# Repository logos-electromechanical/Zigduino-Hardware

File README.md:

Zigduino-Hardware
=================

Hardware repository for the Zigduino

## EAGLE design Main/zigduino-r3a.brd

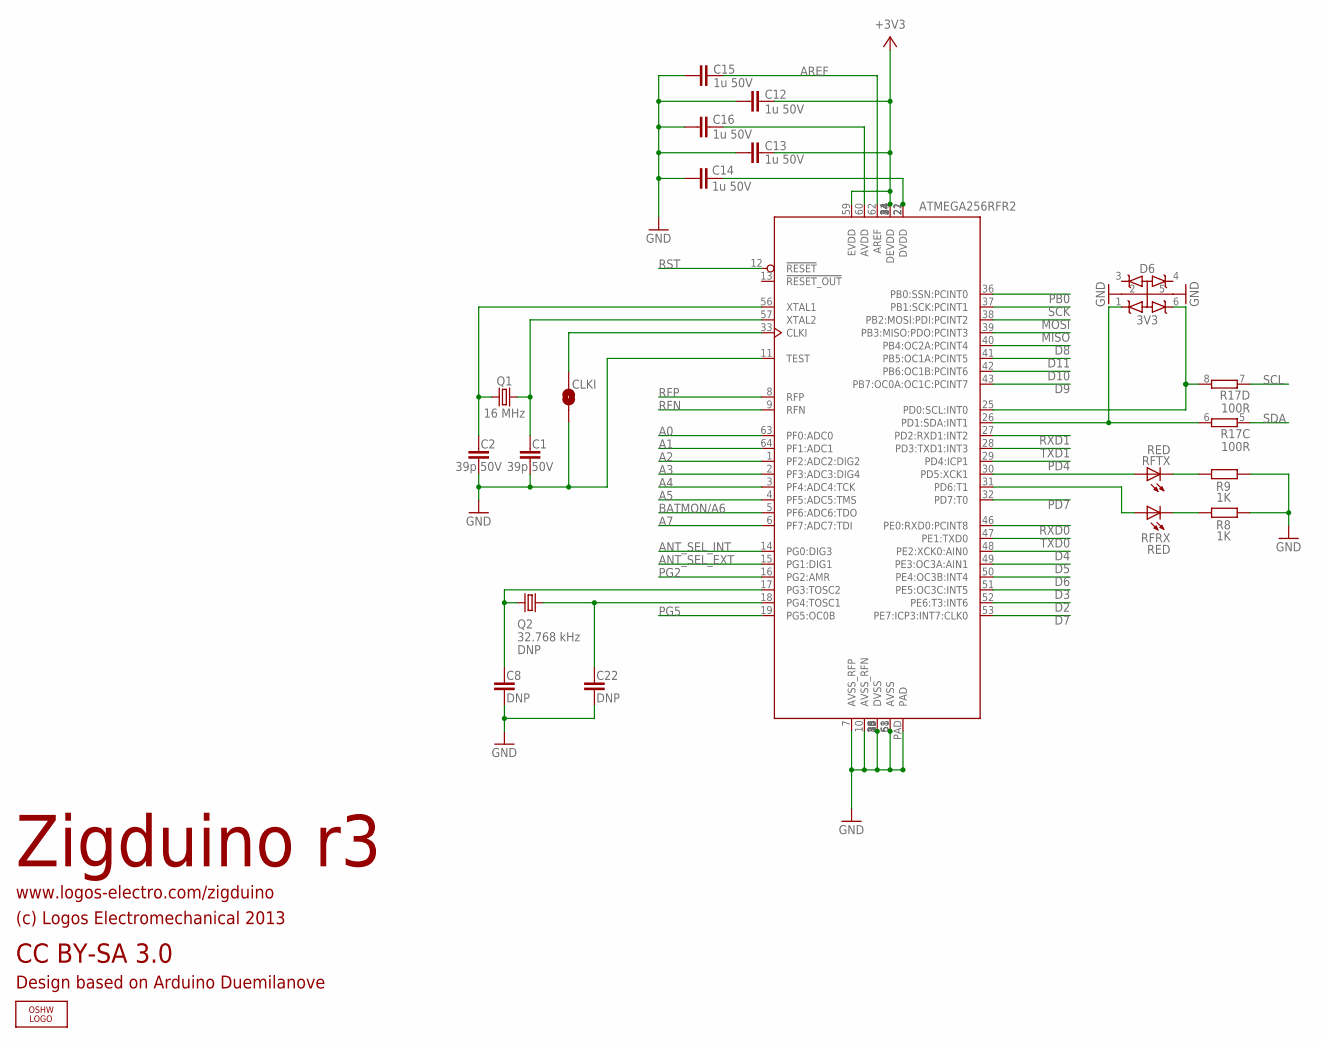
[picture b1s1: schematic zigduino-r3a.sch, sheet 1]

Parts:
C1, C2: 39p 50V; C0603; PARTNO C1608C0G1H390J
C8, C22: DNP; C0603
C12, C13, C14, C15, C16: 1u 50V; C0603
CLKI: SOLDERJUMPERTRACE; SJ_2S-TRACE
D6: 3V3; SC74_INFINEON
LOGO1: OSHW_LOGO_FILLX0200-NT; OSHW_FILLX200_NOTEXT
Q1: 16 MHz; CSM-3X; PARTNO ECS-160-20-3X-TR
Q2: 32.768 kHz; TC26H
R8, R9: 1K; R0603; PARTNO RMCF0603FT1K00
R17: 100R; CTS742C083-RES; PARTNO 742C083101JPTR
RFRX: RED; CHIP-LED0603; PARTNO LTST-C193KRKT-5A
RFTX: RED; CHIP-LED0603; PARTNO LTST-C193KRKT-5A
U3: ATMEGA128RFA1; QFN64; PARTNO ATMEGA128RFA1-ZUR

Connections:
+3V3: C12.1, C13.1, U3.23 (DEVDD), U3.34 (DEVDD), U3.44 (DEVDD), U3.54 (DEVDD), U3.59 (EVDD); also elsewhere on the board
A0: U3.63 (PF0:ADC0); also elsewhere on the board
A1: U3.64 (PF1:ADC1); also elsewhere on the board
A2: U3.1 (PF2:ADC2:DIG2); also elsewhere on the board
A3: U3.2 (PF3:ADC3:DIG4); also elsewhere on the board
A4: U3.3 (PF4:ADC4:TCK); also elsewhere on the board
A5: U3.4 (PF5:ADC5:TMS); also elsewhere on the board
A7: U3.6 (PF7:ADC7:TDI); also elsewhere on the board
ANT_SEL_EXT: U3.15 (PG1:DIG1); also elsewhere on the board
ANT_SEL_INT: U3.14 (PG0:DIG3); also elsewhere on the board
AREF: C15.2, U3.62 (AREF); also elsewhere on the board
BATMON/A6: U3.5 (PF6:ADC6:TDO); also elsewhere on the board
D2: U3.52 (PE6:T3:INT6); also elsewhere on the board
D3: U3.51 (PE5:OC3C:INT5); also elsewhere on the board
D4: U3.48 (PE2:XCK0:AIN0); also elsewhere on the board
D5: U3.49 (PE3:OC3A:AIN1); also elsewhere on the board
D6: U3.50 (PE4:OC3B:INT4); also elsewhere on the board
D7: U3.53 (PE7:ICP3:INT7:CLK0); also elsewhere on the board
D8: U3.40 (PB4:OC2A:PCINT4); also elsewhere on the board
D9: U3.43 (PB7:OC0A:OC1C:PCINT7); also elsewhere on the board
D10: U3.42 (PB6:OC1B:PCINT6); also elsewhere on the board
D11: U3.41 (PB5:OC1A:PCINT5); also elsewhere on the board
GND: C1.1, C2.1, C8.1, C12.2, C13.2, C14.2, C15.1, C16.1, C22.1, CLKI.2, D6.2 (G2), D6.5 (G5), R8.1, R9.1, U3.7 (AVSS_RFP), U3.10 (AVSS_RFN), U3.11 (TEST), U3.20 (DVSS), U3.24 (DVSS), U3.35 (DVSS), U3.45 (DVSS), U3.55 (DVSS), U3.58 (AVSS), U3.61 (AVSS), U3.PAD; also elsewhere on the board
MISO: U3.39 (PB3:MISO:PDO:PCINT3); also elsewhere on the board
MOSI: U3.38 (PB2:MOSI:PDI:PCINT2); also elsewhere on the board
unnamed: R9.2, RFTX.C
unnamed: C1.2, Q1.1, U3.57 (XTAL2)
unnamed: C2.2, Q1.2, U3.56 (XTAL1)
unnamed: D6.6 (Z6), R17.8 (2), U3.25 (PD0:SCL:INT0)
unnamed: D6.1 (Z1), R17.6 (2), U3.26 (PD1:SDA:INT1)
unnamed: R8.2, RFRX.C
unnamed: CLKI.1, U3.33 (CLKI)
unnamed: C14.1, U3.21 (DVDD), U3.22 (DVDD)
unnamed: C16.2, U3.60 (AVDD)
unnamed: C8.2, Q2.2, U3.17 (PG3:TOSC2)
unnamed: C22.2, Q2.1, U3.18 (PG4:TOSC1)
PB0: U3.36 (PB0:SSN:PCINT0); also elsewhere on the board
PD4: U3.29 (PD4:ICP1); also elsewhere on the board
PD7: U3.32 (PD7:T0); also elsewhere on the board
PG2: U3.16 (PG2:AMR); also elsewhere on the board
PG5: U3.19 (PG5:OC0B); also elsewhere on the board
RFN: U3.9 (RFN); also elsewhere on the board
RFP: U3.8 (RFP); also elsewhere on the board
RFRX: RFRX.A, U3.31 (PD6:T1)
RFTX: RFTX.A, U3.30 (PD5:XCK1)
RST: U3.12 (!RESET!); also elsewhere on the board
RXD0: U3.46 (PE0:RXD0:PCINT8); also elsewhere on the board
RXD1: U3.27 (PD2:RXD1:INT2); also elsewhere on the board
SCK: U3.37 (PB1:SCK:PCINT1); also elsewhere on the board
SCL: R17.7 (1); also elsewhere on the board
SDA: R17.5 (1); also elsewhere on the board
TXD0: U3.47 (PE1:TXD0); also elsewhere on the board
TXD1: U3.28 (PD3:TXD1:INT3); also elsewhere on the board

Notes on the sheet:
Zigduino r3
CC BY-SA 3.0
(c) Logos Electromechanical 2013
www.logos-electro.com/zigduino
ATMEGA256RFR2
Design based on Arduino Duemilanove
DNP

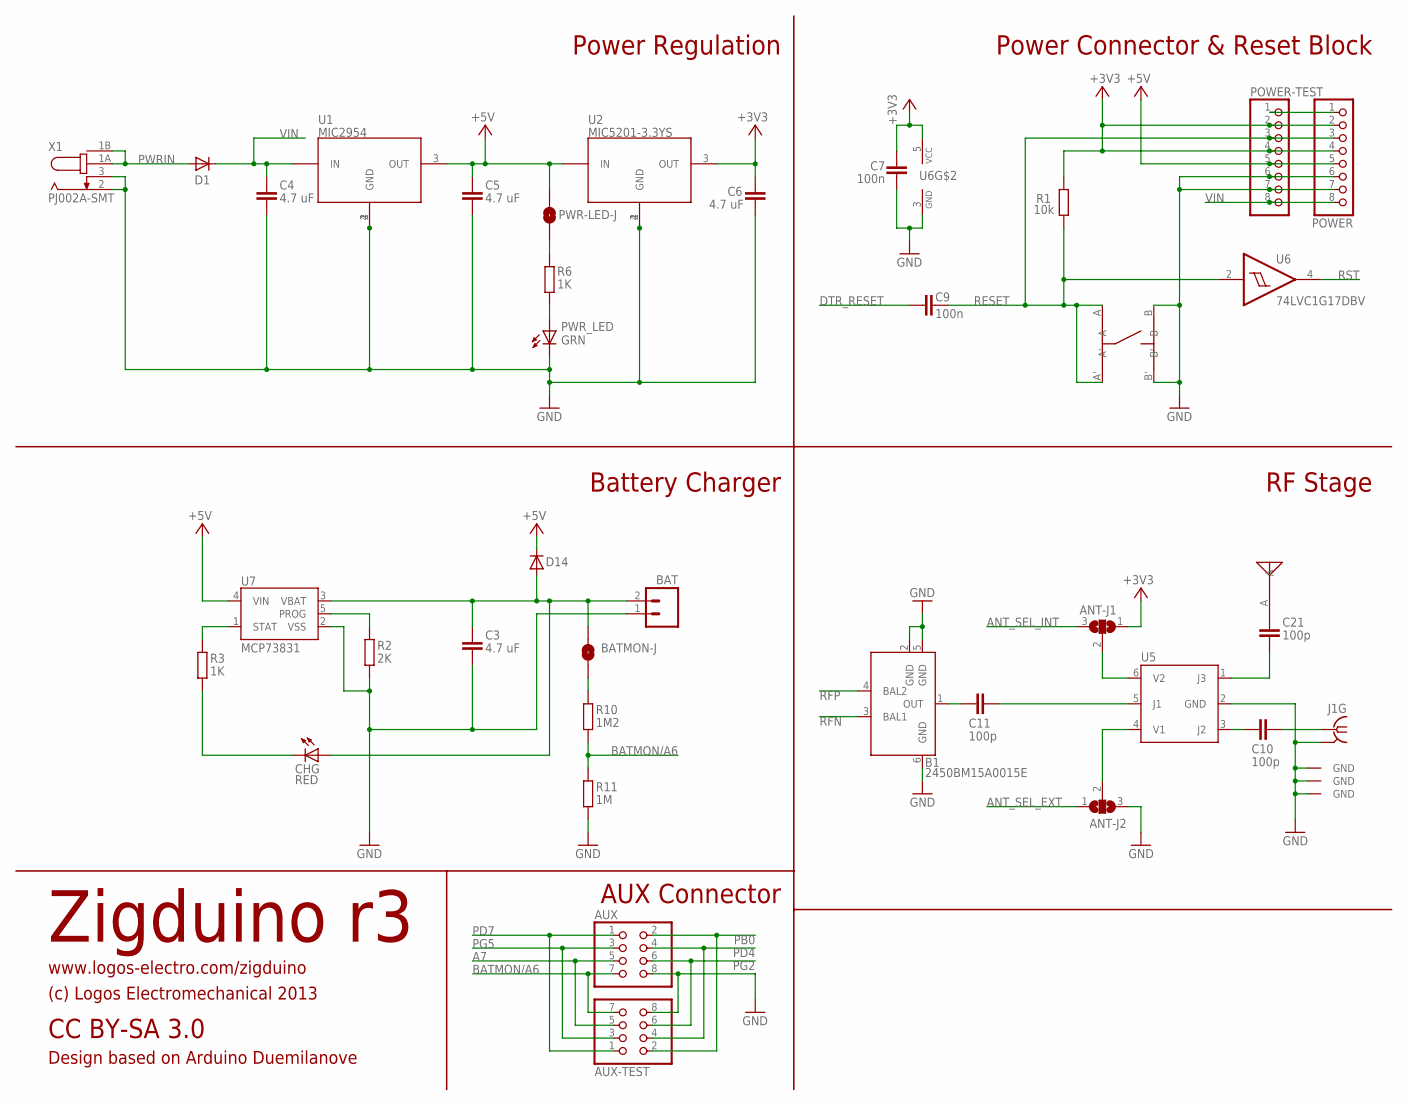
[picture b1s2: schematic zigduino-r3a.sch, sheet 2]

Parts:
ANT1: MOLEX-ANT; PARTNO 0479480001
ANT-J1: SOLDERJUMPER_2WAYSHORT1&2; SJ_3_SHORT1&2
ANT-J2: SOLDERJUMPER_2WAYSHORT2&3; SJ_3_SHORT2&3
AUX: PINHD-2X4_2.54-SMD; 2X04SMD
AUX-TEST: PINHD-2X4TEST; 2X04-TEST
B1: 2450BM15A0015E; WURTH-BALUN
BAT: M02-JST-2MM-SMT; S2B-PH; PARTNO S2B-PH-SM4-TB(LF)(SN)
BATMON-J: SOLDERJUMPERTRACE; SJ_2S-TRACE
C3, C4, C5, C6: 4.7 uF; C1206; PARTNO C3216Y5V1H475Z
C7, C9: 100n; C0603; PARTNO CC0603MRY5V9BB104
C10, C11, C21: 100p; C0603
CHG: RED; CHIP-LED0603; PARTNO LTST-C193KRKT-5A
D1, D14: DIODESOD-123; SOD-123; PARTNO B150B-13-F
J1: CONNREVSMA003.062; EDGE-RSMA
POWER: PINHD-1X8_2.54-SMD; 1X08SMD; PARTNO 19743
POWER-TEST: PINHD-1X8TEST; 1X08-TEST
PWR-LED-J: SOLDERJUMPERTRACE; SJ_2S-TRACE
PWR_LED: GRN; CHIP-LED0603; PARTNO LTST-C193KGKT-5A
R1: 10k; R0603; PARTNO RMCF0603FT10K0
R2: 2K; R0603; PARTNO RC0603FR-072KL
R3, R6: 1K; R0603; PARTNO RMCF0603FT1K00
R10: 1M2; R0603; PARTNO ERJ-3EKF1204V
R11: 1M; R0603; PARTNO ERJ-3EKF1004V
SW1: EVQ-PSD02K; EVQPSD02K; PARTNO EVQ-PSD02K
U1: MIC2954; SOT223; PARTNO MIC2954-03WS-TR
U2: MIC5201-3.3YS; SOT223; PARTNO MIC5201-3.3YS TR
U5: AS222-92LF; SC70-6L
U6: 74LVC1G17DBV; SOT23-5; PARTNO SN74LVC1G17DBVR
U7: MCP73831; SOT23-5; PARTNO MCP73831T-2ACI/OT
X1: PJ002A-SMT; PARTNO PJ-002AH-SMT

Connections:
+3V3: ANT-J1.1, C6.1, C7.2, POWER.2, POWER.4, POWER-TEST.2, POWER-TEST.4, R1.2, U2.3 (OUT), U6.5 (VCC); also elsewhere on the board
+5V: C5.1, D14.C, POWER.5, POWER-TEST.5, PWR-LED-J.2, U1.3 (OUT), U2.1 (IN), U7.4 (VIN); also elsewhere on the board
A7: AUX.5, AUX-TEST.5; also elsewhere on the board
ANT_SEL_EXT: ANT-J2.1; also elsewhere on the board
ANT_SEL_INT: ANT-J1.3; also elsewhere on the board
BATMON/A6: AUX.7, AUX-TEST.7, R10.2, R11.1; also elsewhere on the board
DTR_RESET: C9.1; also elsewhere on the board
GND: ANT-J2.3, AUX.8, AUX-TEST.8, B1.2 (GND), B1.5 (GND), B1.6 (GND), BAT.1, C3.2, C4.2, C5.2, C6.2, C7.1, J1.SHIELD@0 (GND), J1.SHIELD@1 (GND), J1.SHIELD@2 (GND), J1.SHIELD@3 (GND), POWER.6, POWER.7, POWER-TEST.6, POWER-TEST.7, PWR_LED.C, R2.1, R11.2, SW1.B, SW1.B', U1.2 (GND), U1.4 (GND), U2.2 (GND), U2.4 (GND), U5.2 (GND), U6.3 (GND), U7.2 (VSS), X1.2, X1.3; also elsewhere on the board
unnamed: PWR_LED.A, R6.2
unnamed: PWR-LED-J.1, R6.1
unnamed: BATMON-J.1, R10.1
unnamed: B1.1 (OUT), C11.2
unnamed: C11.1, U5.5 (J1)
unnamed: C10.2, U5.3 (J2)
unnamed: R2.2, U7.5 (PROG)
unnamed: R3.1, U7.1 (STAT)
unnamed: CHG.C, R3.2
unnamed: C21.2, U5.1 (J3)
unnamed: C10.1, J1.CENTER (1)
unnamed: POWER.1, POWER-TEST.1
unnamed: ANT1.A, C21.1
unnamed: ANT-J2.2, U5.4 (V1)
unnamed: ANT-J1.2, U5.6 (V2)
PB0: AUX.2, AUX-TEST.2; also elsewhere on the board
PD4: AUX.4, AUX-TEST.4; also elsewhere on the board
PD7: AUX.1, AUX-TEST.1; also elsewhere on the board
PG2: AUX.6, AUX-TEST.6; also elsewhere on the board
PG5: AUX.3, AUX-TEST.3; also elsewhere on the board
PWRIN: D1.A, X1.1A, X1.1B
RESET: C9.2, POWER.3, POWER-TEST.3, R1.1, SW1.A, SW1.A', U6.2 (I); also elsewhere on the board
RFN: B1.3 (BAL1); also elsewhere on the board
RFP: B1.4 (BAL2); also elsewhere on the board
RST: U6.4 (O); also elsewhere on the board
VBAT: BAT.2, BATMON-J.2, C3.1, CHG.A, D14.A, U7.3 (VBAT); also elsewhere on the board
VIN: C4.1, D1.C, POWER.8, POWER-TEST.8, U1.1 (IN)

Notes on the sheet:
Zigduino r3
CC BY-SA 3.0
(c) Logos Electromechanical 2013
www.logos-electro.com/zigduino
Design based on Arduino Duemilanove
AUX Connector
Battery Charger
Power Regulation
RF Stage
Power Connector & Reset Block

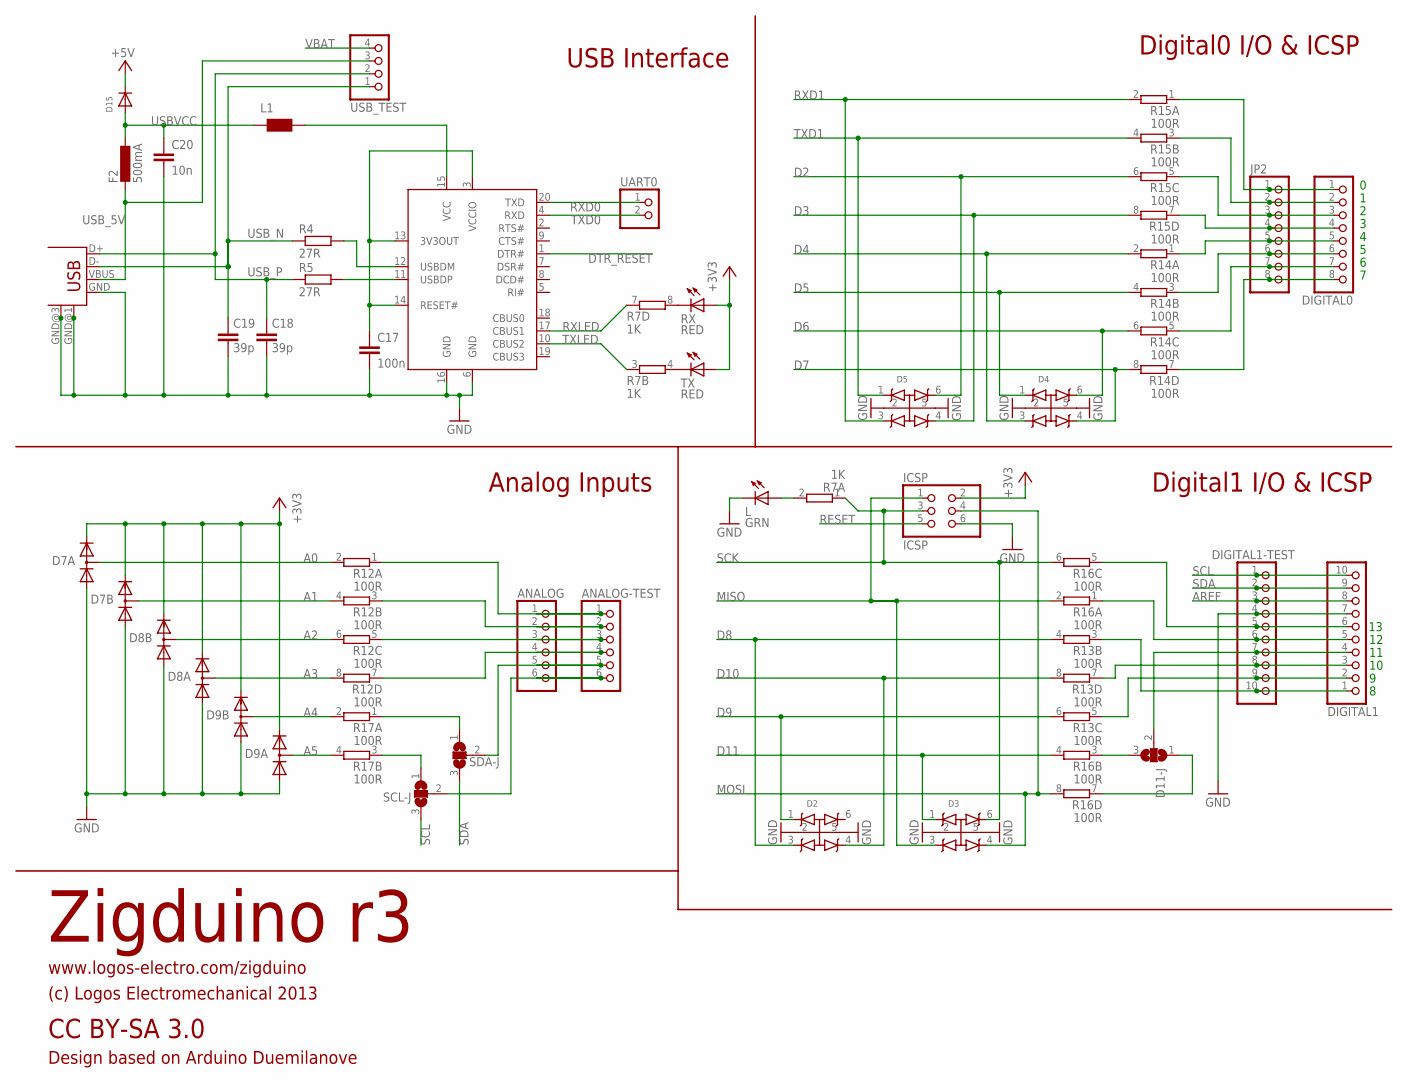
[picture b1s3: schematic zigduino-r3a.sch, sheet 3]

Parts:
ANALOG: PINHD-1X6_2.54-SMD; 1X06SMD; PARTNO 19742
ANALOG-TEST: PINHD-1X6TEST; 1X06-TEST
C17: 100n; C0603; PARTNO CC0603MRY5V9BB104
C18, C19: 39p; C0603; PARTNO C1608C0G1H390J
C20: 10n; C0603; PARTNO GRM188R71H103KA01D
D2, D3, D4, D5: PESD3V3S4UD; SC74_INFINEON
D7, D8, D9: SD103ASDM; SOT26; PARTNO SD103ASDM-7
D11-J: SOLDERJUMPER_2WAYSHORT2&3; SJ_3_SHORT2&3
D15: DIODESOD-123; SOD-123; PARTNO B150B-13-F
DIGITAL0: PINHD-1X8_2.54-SMD; 1X08SMD; PARTNO 19743
DIGITAL1: PINHD-1X10_2.54-SMD; 1X10SMD; PARTNO 20083
DIGITAL1-TEST: PINHD-1X10TEST; 1X10-TEST
F2: 500mA; L1812; PARTNO MF-MSMF050-2
ICSP: ICSP; 2X03; PARTNO 961206-6404-AR
JP2: PINHD-1X8TEST; 1X08-TEST
L: GRN; CHIP-LED0603; PARTNO LTST-C193KGKT-5A
L1: WE-CBF_0805; 0805; PARTNO MI0805K400R-10
R4, R5: 27R; R0603; PARTNO RC0603JR-0727RL
R7: 1K; CTS742C083-RES; PARTNO 742C083102JPTR
R12, R13, R14, R15, R16, R17: 100R; CTS742C083-RES; PARTNO 742C083101JPTR
RX: RED; CHIP-LED0603; PARTNO LTST-C193KRKT-5A
SCL-J: SOLDERJUMPER_2WAYSHORT2&3; SJ_3_SHORT2&3
SDA-J: SOLDERJUMPER_2WAYSHORT2&3; SJ_3_SHORT2&3
TX: RED; CHIP-LED0603; PARTNO LTST-C193KRKT-5A
U4: FT231XS-R; SSOP20; PARTNO FT231XS-R
UART0: PINHD-1X2; 1X02; PARTNO 00522
USB: USB-MB-S; PARTNO 20236
USB_TEST: PINHD-1X4TEST; 1X04-TEST

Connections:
+3V3: D7.2 (C), D7.5 (C), D8.2 (C), D8.5 (C), D9.2 (C), D9.5 (C), ICSP.2, RX.A, TX.A; also elsewhere on the board
+5V: D15.C; also elsewhere on the board
A0: D7.4 (AC), R12.2; also elsewhere on the board
A1: D7.1 (AC), R12.4 (2); also elsewhere on the board
A2: D8.1 (AC), R12.6 (2); also elsewhere on the board
A3: D8.4 (AC), R12.8 (2); also elsewhere on the board
A4: D9.1 (AC), R17.2; also elsewhere on the board
A5: D9.4 (AC), R17.4 (2); also elsewhere on the board
AREF: DIGITAL1.8, DIGITAL1-TEST.3; also elsewhere on the board
D2: D5.6 (Z6), R15.6 (2); also elsewhere on the board
D3: D5.4 (Z4), R15.8 (2); also elsewhere on the board
D4: D4.3 (Z3), R14.2; also elsewhere on the board
D5: D4.1 (Z1), R14.4 (2); also elsewhere on the board
D6: D4.6 (Z6), R14.6 (2); also elsewhere on the board
D7: D4.4 (Z4), R14.8 (2); also elsewhere on the board
D8: D2.3 (Z3), R13.4 (2); also elsewhere on the board
D9: D2.1 (Z1), R13.6 (2); also elsewhere on the board
D10: D2.4 (Z4), R13.8 (2); also elsewhere on the board
D11: D3.1 (Z1), R16.4 (2); also elsewhere on the board
DTR_RESET: U4.1 (DTR#); also elsewhere on the board
GND: C17.2, C18.2, C19.2, C20.2, D2.2 (G2), D2.5 (G5), D3.2 (G2), D3.5 (G5), D4.2 (G2), D4.5 (G5), D5.2 (G2), D5.5 (G5), D7.3 (A), D7.6 (A), D8.3 (A), D8.6 (A), D9.3 (A), D9.6 (A), DIGITAL1.7, DIGITAL1-TEST.4, ICSP.6, L.C, U4.6 (GND), U4.16 (GND), USB.GND, USB.GND@1 (GND), USB.GND@3 (GND); also elsewhere on the board
MISO: D3.3 (Z3), ICSP.1, R16.2; also elsewhere on the board
MOSI: D3.4 (Z4), ICSP.4, R16.8 (2); also elsewhere on the board
MOSI-PIN: D11-J.1, R16.7 (1)
unnamed: L.A, R7.2
unnamed: ANALOG.5, ANALOG-TEST.5, SDA-J.2
unnamed: DIGITAL0.3, JP2.3, R15.5 (1)
unnamed: DIGITAL1.5, DIGITAL1-TEST.6, R16.1
unnamed: DIGITAL0.5, JP2.5, R14.1
unnamed: DIGITAL0.7, JP2.7, R14.5 (1)
unnamed: DIGITAL0.6, JP2.6, R14.3 (1)
unnamed: DIGITAL0.4, JP2.4, R15.7 (1)
unnamed: DIGITAL0.8, JP2.8, R14.7 (1)
unnamed: DIGITAL1.6, DIGITAL1-TEST.5, R16.5 (1)
unnamed: R7.4 (2), TX.C
unnamed: C17.1, U4.3 (VCCIO), U4.13 (3V3OUT), U4.14 (RESET#)
unnamed: R7.8 (2), RX.C
unnamed: R4.2, U4.12 (USBDM)
unnamed: R5.2, U4.11 (USBDP)
unnamed: L1.2, U4.15 (VCC)
unnamed: ANALOG.6, ANALOG-TEST.6, SCL-J.2
unnamed: R17.1, SDA-J.1
unnamed: ANALOG.1, ANALOG-TEST.1, R12.1
unnamed: ANALOG.2, ANALOG-TEST.2, R12.3 (1)
unnamed: ANALOG.3, ANALOG-TEST.3, R12.5 (1)
unnamed: ANALOG.4, ANALOG-TEST.4, R12.7 (1)
unnamed: R17.3 (1), SCL-J.1
unnamed: DIGITAL1.1, DIGITAL1-TEST.10, R13.3 (1)
unnamed: D11-J.2, DIGITAL1.4, DIGITAL1-TEST.7
unnamed: DIGITAL1.2, DIGITAL1-TEST.9, R13.5 (1)
unnamed: DIGITAL0.1, JP2.1, R15.1
unnamed: DIGITAL0.2, JP2.2, R15.3 (1)
PWM-10: DIGITAL1.3, DIGITAL1-TEST.8, R13.7 (1)
PWM-11: D11-J.3, R16.3 (1)
RESET: ICSP.5; also elsewhere on the board
RXD0: U4.20 (TXD), UART0.1; also elsewhere on the board
RXD1: D5.3 (Z3), R15.2; also elsewhere on the board
RXLED: R7.7 (1), U4.17 (CBUS1)
SCK: D3.6 (Z6), ICSP.3, R7.1, R16.6 (2); also elsewhere on the board
SCL: DIGITAL1.10, DIGITAL1-TEST.1, SCL-J.3; also elsewhere on the board
SDA: DIGITAL1.9, DIGITAL1-TEST.2, SDA-J.3; also elsewhere on the board
TXD0: U4.4 (RXD), UART0.2; also elsewhere on the board
TXD1: D5.1 (Z1), R15.4 (2); also elsewhere on the board
TXLED: R7.3 (1), U4.10 (CBUS2)
USBVCC: C20.1, D15.A, F2.1, L1.1
USB_5V: F2.2, USB.VBUS, USB_TEST.3
USB_N: C19.1, R4.1, USB.D-, USB_TEST.1
USB_P: C18.1, R5.1, USB.D+, USB_TEST.2
VBAT: USB_TEST.4; also elsewhere on the board

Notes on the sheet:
Zigduino r3
CC BY-SA 3.0
(c) Logos Electromechanical 2013
www.logos-electro.com/zigduino
Design based on Arduino Duemilanove
Analog Inputs
USB Interface
Digital1 I/O & ICSP
Digital0 I/O & ICSP

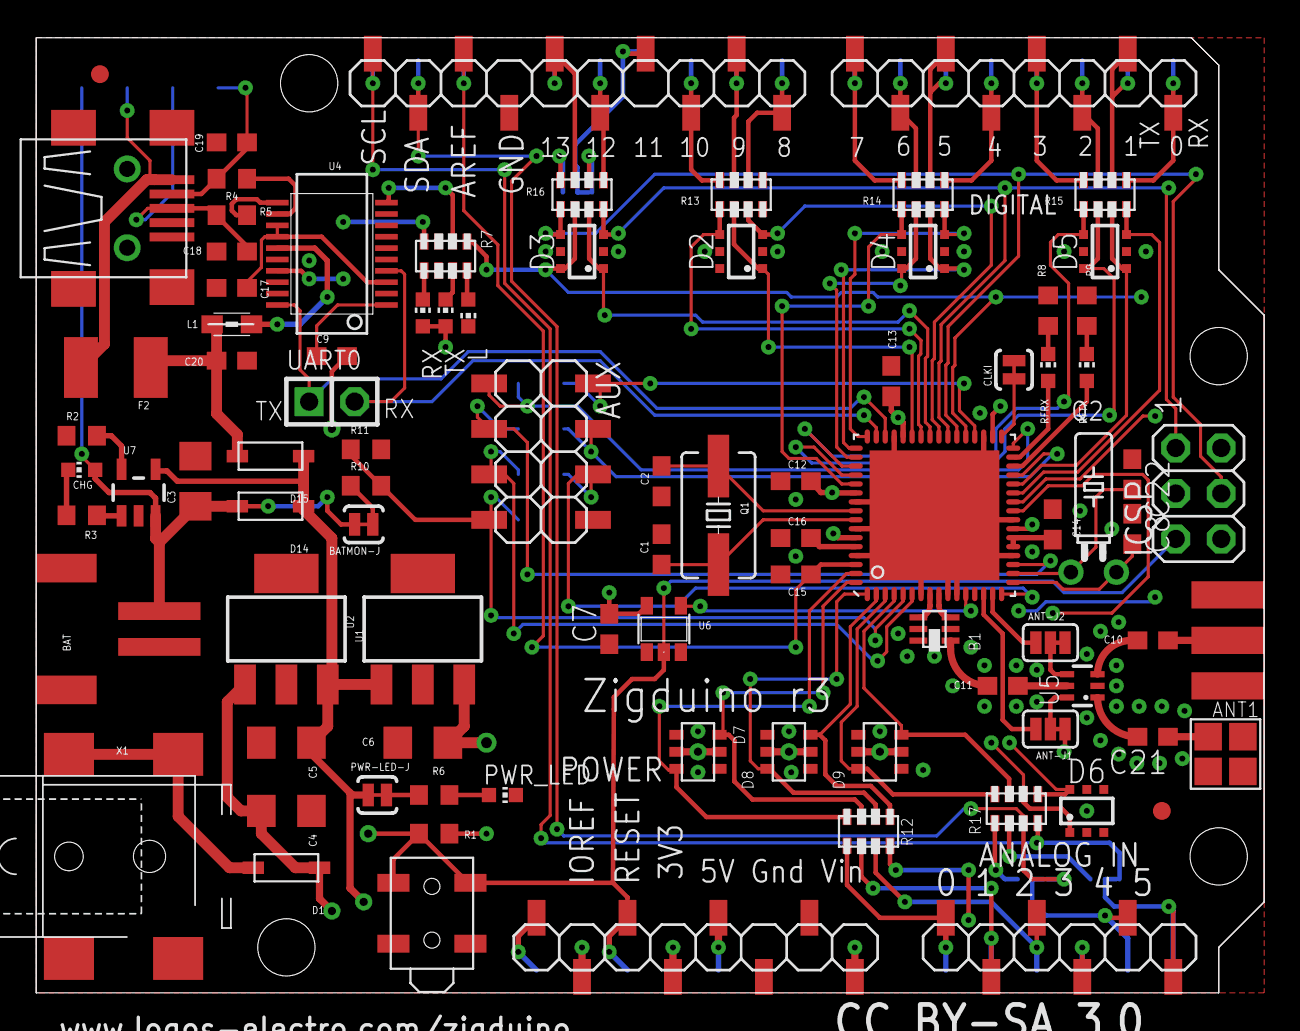
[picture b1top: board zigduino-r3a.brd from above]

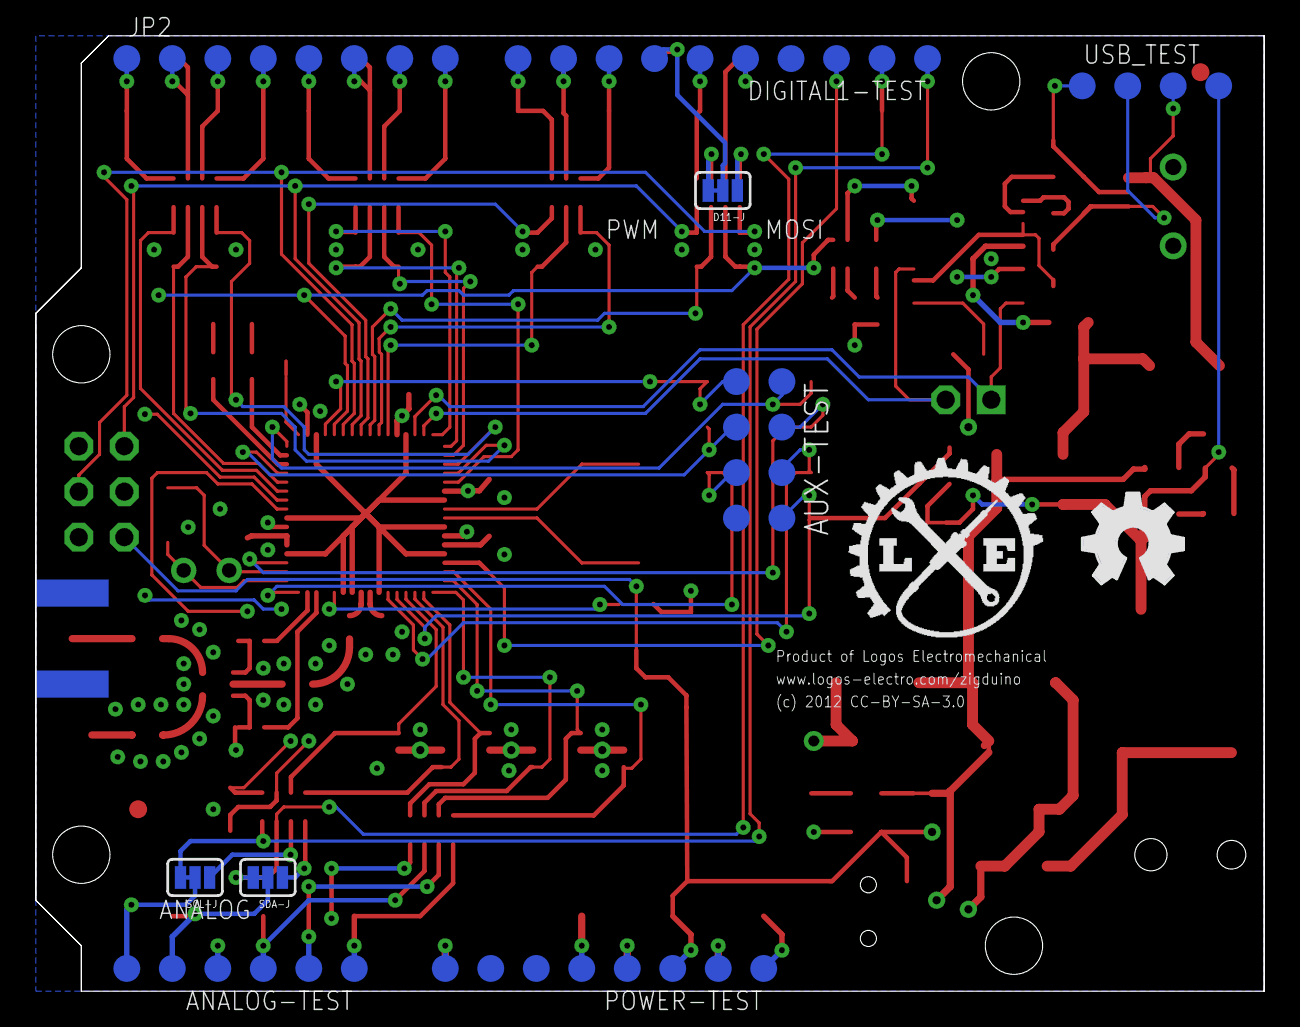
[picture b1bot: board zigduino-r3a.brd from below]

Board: 4 copper layers, 68.6 x 53.3 mm, 100 parts (11 on the bottom side), 111 nets.

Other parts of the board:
U$3, U$5: FIDUCIAL_G10
U$4: LOGO-SM

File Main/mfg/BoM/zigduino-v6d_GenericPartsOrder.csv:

Manufacturer Part Number,Description,Qty-1,Part References,Value
B150B-13-F,DIODE SCHOTTKY 50V 1A SMB,3,"D1, D14, D15",
MI0805K400R-10,FERRITE 1.5A 40 OHM 0805 SMD,1,L1,
S2B-PH-SM4-TB(LF)(SN),CONN HEADER PH SIDE 2POS 2MM SMD,1,JP1,
742C083102JPTR,RES ARRAY 1K OHM 8TERM 4RES SMD,1,R7,1K
RMCF0603FT1K00,RES 1K OHM 1/10W 1% 0603 SMD,4,"R3, R6, R8, R9",1K
ERJ-3EKF1004V,RES 1.00M OHM 1/10W 1% 0603 SMD,1,R11,1M
ERJ-3EKF1204V,RES 1.20M OHM 1/10W 1% 0603 SMD,1,R10,1M2
RC0603FR-072KL,RES 2.00K OHM 1/10W 1% 0603 SMD,1,R2,2K
C3216Y5V1H475Z,CAP CER 4.7UF 50V Y5V 1206,4,"C3, C4, C5, C6",4.7 uF
RMCF0603FT10K0,RES 10K OHM 1/10W 1% 0603 SMD,1,R1,10k
GRM188R71H103KA01D,CAP CER 10000PF 50V 10% X7R 0603,1,C20,10n
ECS-160-20-3X-TR,CRYSTAL 16.00000 MHZ 20PF SMD,1,Q1,16 MHz
GQM1885C1H220JB01D,CAP CER 22PF 50V 5% C0G 0603,2,"C10, C11",22p
RC0603JR-0727RL,311-27GRTR-ND,2,"R4, R5",27R
C1608C0G1H390J,CAP CER 39PF 50V 5% NP0 0603,4,"C1, C2, C18, C19",39p
SN74LVC1G17DBVR,IC BUFFER SCHMIT TRIG SOT235,1,U6,74LVC1G17DBV
742C083101JPTR,RES ARRAY 100 OHM 8TERM 4RES SMD,6,"R12, R13, R14, R15, R16, R17",100R
CC0603MRY5V9BB104,CAP CERAMIC .1UF 50V Y5V 0603,7,"C9, C12, C13, C14, C15, C16, C17",100n
MF-MSMF050-2,PTC RESETTABLE .50A 15V 1812,1,F2,500mA
ATMEGA128RFA1-ZUR,IC AVR MCU 2.4GHZ XCEIVER 64QFN,1,U3,ATMEGA128RFA1
EVQ-PSD02K,SWITCH TACTILE SPST-NO 0.05A 12V,1,SW1,EVQ-PSD02K
FT231XS-R,IC USB SERIAL FULL UART SSOP-20,1,U4,FT231XS-R
LTST-C193KGKT-5A,LED GREEN RECT CLEAR 0603,2,"L, PWR",GRN
961206-6404-AR,CONN HEADER VERT DUAL 6POS GOLD,0,ICSP(DNP),ICSP
MCP73831T-2ACI/OT,IC CONTROLLR LI-ION 4.2V SOT23-5,1,U7,MCP73831
MIC2954-03WS-TR,IC REG LDO 250MA 5V 1.0% SOT223,1,U1,MIC2954
MIC5201-3.3YS TR,IC REG LDO 200MA 3.3V 1% SOT223,1,U2,MIC5201-3.3YS TR
479480001,ANTENNA 2.4GHZ 50 OHMS SMD,1,ANT1,MOLEX-ANT
PJ-002AH-SMT,CONN POWER JACK 2.1X5.5MM HI CUR,1,X1,PJ002A-SMT
LTST-C193KRKT-5A,LED RED RECT CLEAR 0603,5,"CHG, RFRX, RFTX, RX, TX",RED
SD103ASDM-7,DIODE SCHOTTKY ARRAY 40V SOT26,12,"D2, D3, D4, D5, D6, D7, D8, D9, D10, D11, D12, D13",SD103ASDM
20236,MINI USB CONNECTOR ,1,USB,USB-MB-S
748421245,BALUN EMBER351 & 357 0805 SMD,1,B1,WUERTH-748421245

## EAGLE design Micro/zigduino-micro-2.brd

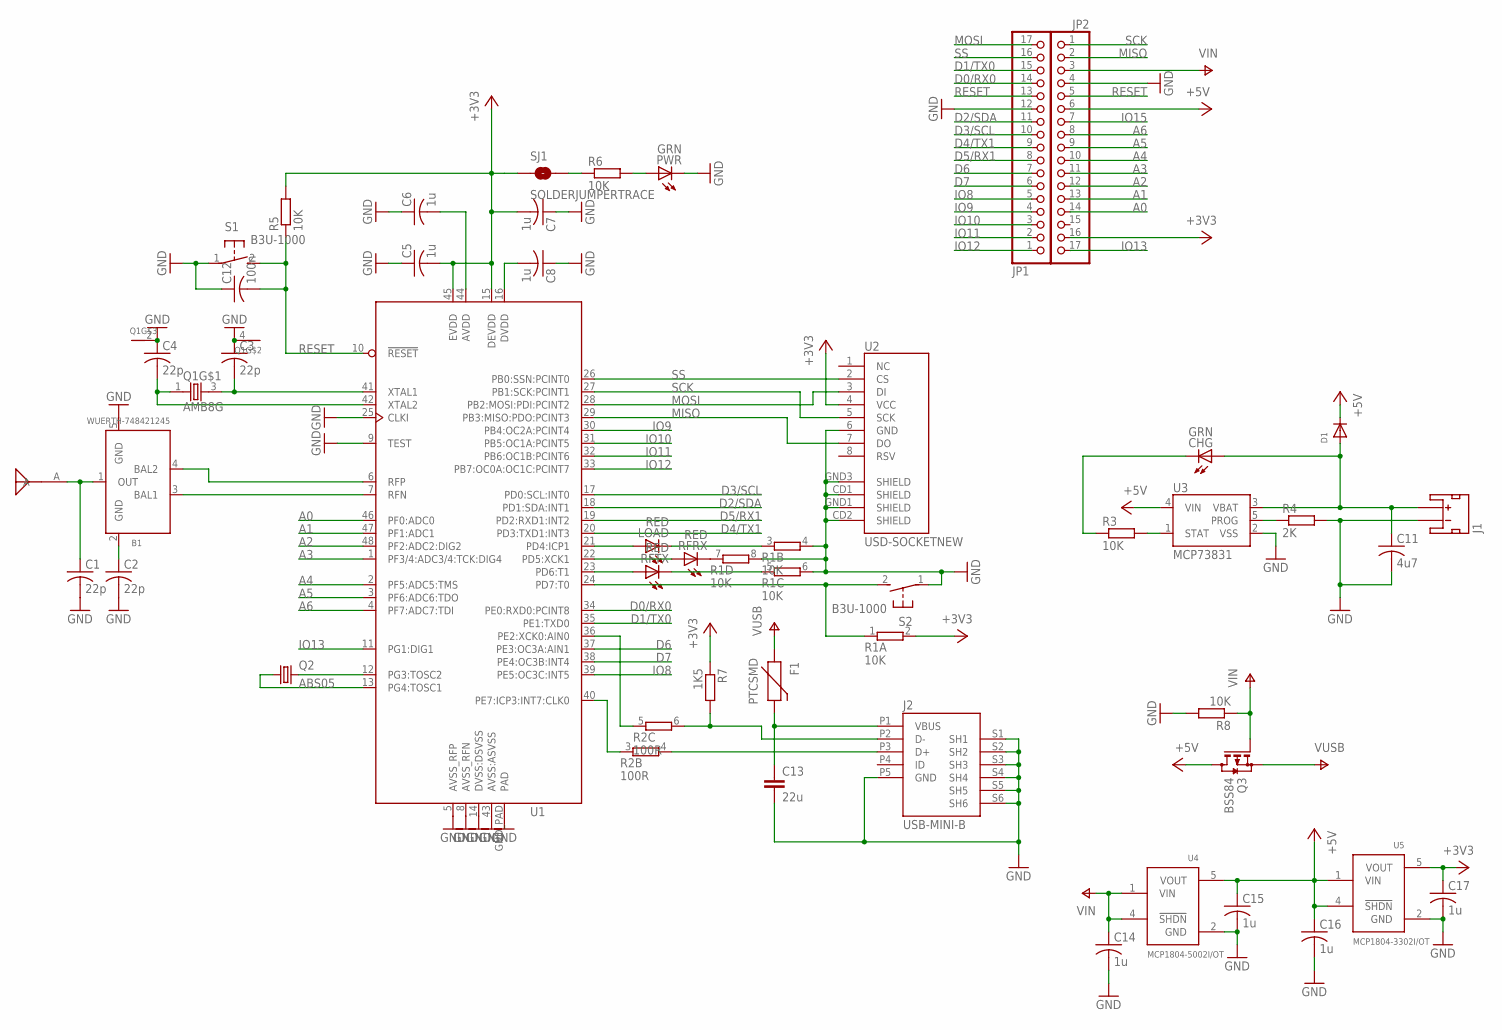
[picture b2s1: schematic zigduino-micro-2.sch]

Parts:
ANT1: ATMEGA128RFA1_MOLEX-ANT
B1: WUERTH-748421245; WURTH-BALUN
C1, C2, C3, C4: 22p; C0603
C5, C6, C7, C8, C14, C15, C16, C17: 1u; C0603
C11: 4u7; C0603
C12: 100n; C0603
C13: 22u; C0805
CHG: GRN; CHIPLED_0603
D1: DIODESOD-123; SOD-123
F1: PTCSMD; PTC-1206
J1: JST_2MM_MALE; JST-2-SMD
J2: USB-MINI-B; SMARTPRJ_CON2_USB_MICRO_B_AT
JP1, JP2: PINHD-1X17_2.54-SMD; 1X17SMD
LOAD: RED; CHIPLED_0603
PWR: GRN; CHIPLED_0603
Q1: AMB8G; ABM8G
Q2: ABS05
Q3: BSS84; SOT23
R1: 10K; CTS742C083-RES
R2: 100R; CTS742C083-RES
R3, R5, R6, R8: 10K; R0603
R4: 2K; R0603
R7: 1K5; R0603
RFRX: RED; CHIPLED_0603
RFTX: RED; CHIPLED_0603
S1, S2: B3U-1000; B3U
SJ1: SOLDERJUMPERTRACE; SJ_2S-TRACE
U1: ATMEGA1284RFR2; QFN48
U2: USD-SOCKETNEW; MICRO-SD-SOCKET-PP
U3: MCP73831; SOT23-5
U4: MCP1804-5002I/OT; SOT23-5L
U5: MCP1804-3302I/OT; SOT23-5L

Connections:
+3V3: C5.2, C7.2, C17.1, JP2.16, R1.2, R5.2, R7.1, SJ1.1, U1.15 (DEVDD), U1.45 (EVDD), U2.4 (VCC), U5.5 (VOUT)
+5V: C15.1, C16.1, D1.C, JP2.6, Q3.3 (D), U3.4 (VIN), U4.5 (VOUT), U5.1 (VIN), U5.4 (!SHDN!)
A0: JP2.14, U1.46 (PF0:ADC0)
A1: JP2.13, U1.47 (PF1:ADC1)
A2: JP2.12, U1.48 (PF2:ADC2:DIG2)
A3: JP2.11, U1.1 (PF3/4:ADC3/4:TCK:DIG4)
A4: JP2.10, U1.2 (PF5:ADC5:TMS)
A5: JP2.9, U1.3 (PF6:ADC6:TDO)
A6: JP2.8, U1.4 (PF7:ADC7:TDI)
D0/RX0: JP1.14, U1.34 (PE0:RXD0:PCINT8)
D1/TX0: JP1.15, U1.35 (PE1:TXD0)
D2/SDA: JP1.11, U1.18 (PD1:SDA:INT1)
D3/SCL: JP1.10, U1.17 (PD0:SCL:INT0)
D4/TX1: JP1.9, U1.20 (PD3:TXD1:INT3)
D5/RX1: JP1.8, U1.19 (PD2:RXD1:INT2)
D6: JP1.7, U1.37 (PE3:OC3A:AIN1)
D7: JP1.6, U1.38 (PE4:OC3B:INT4)
GND: B1.5 (GND), C1.2, C2.2, C3.1, C4.1, C5.1, C6.1, C7.1, C8.1, C11.2, C12.1, C13.2, C14.2, C15.2, C16.2, C17.2, J1.1 (-), J2.P5 (GND), J2.S1 (SH1), J2.S2 (SH2), J2.S3 (SH3), J2.S4 (SH4), J2.S5 (SH5), J2.S6 (SH6), JP1.12, JP2.4, PWR.C, Q1.2 (PIN), Q1.4 (PIN), R1.4 (2), R1.6 (2), R1.8 (2), R4.2, R8.2, S1.1, S2.1, U1.5 (AVSS_RFP), U1.8 (AVSS_RFN), U1.9 (TEST), U1.14 (DVSS:DSVSS), U1.25 (CLKI), U1.43 (AVSS:ASVSS), U1.GND_PAD (PAD), U2.6 (GND), U2.CD1 (SHIELD), U2.CD2 (SHIELD), U2.GND1 (SHIELD), U2.GND3 (SHIELD), U3.2 (VSS), U4.2 (GND), U5.2 (GND)
IO8: JP1.5, U1.39 (PE5:OC3C:INT5)
IO9: JP1.4, U1.30 (PB4:OC2A:PCINT4)
IO10: JP1.3, U1.31 (PB5:OC1A:PCINT5)
IO11: JP1.2, U1.32 (PB6:OC1B:PCINT6)
IO12: JP1.1, U1.33 (PB7:OC0A:OC1C:PCINT7)
IO13: JP2.17, U1.11 (PG1:DIG1)
IO15: JP2.7
MISO: JP2.2, U1.29 (PB3:MISO:PDO:PCINT3), U2.7 (DO)
MOSI: JP1.17, U1.28 (PB2:MOSI:PDI:PCINT2), U2.3 (DI)
unnamed: ANT1.A, B1.1 (OUT), C1.1
unnamed: B1.3 (BAL1), U1.7 (RFN)
unnamed: B1.4 (BAL2), U1.6 (RFP)
unnamed: B1.2 (GND), C2.1
unnamed: C3.2, Q1.3 (2), U1.41 (XTAL1)
unnamed: Q2.2, U1.12 (PG3:TOSC2)
unnamed: C4.2, Q1.1, U1.42 (XTAL2)
unnamed: C6.2, U1.44 (AVDD)
unnamed: Q2.1, U1.13 (PG4:TOSC1)
unnamed: C8.2, U1.16 (DVDD)
unnamed: LOAD.A, U1.21 (PD4:ICP1)
unnamed: R2.3 (1), U1.40 (PE7:ICP3:INT7:CLK0)
unnamed: R2.5 (1), U1.36 (PE2:XCK0:AIN0)
unnamed: RFTX.A, U1.23 (PD6:T1)
unnamed: PWR.A, R6.2
unnamed: RFRX.A, U1.22 (PD5:XCK1)
unnamed: R1.7 (1), RFRX.C
unnamed: R1.5 (1), RFTX.C
unnamed: J2.P2 (D-), R2.6 (2), R7.2
unnamed: J2.P3 (D+), R2.4 (2)
unnamed: LOAD.C, R1.3 (1)
unnamed: R1.1, S2.2, U1.24 (PD7:T0)
unnamed: R6.1, SJ1.2
unnamed: C11.1, CHG.A, D1.A, J1.2 (+), U3.3 (VBAT)
unnamed: R3.2, U3.1 (STAT)
unnamed: R4.1, U3.5 (PROG)
unnamed: C13.1, F1.2, J2.P1 (VBUS)
unnamed: CHG.C, R3.1
RESET: C12.2, JP1.13, JP2.5, R5.1, S1.2, U1.10 (!RESET!)
SCK: JP2.1, U1.27 (PB1:SCK:PCINT1), U2.5 (SCK)
SS: JP1.16, U1.26 (PB0:SSN:PCINT0), U2.2 (CS)
VIN: C14.1, JP2.3, Q3.1 (G), R8.1, U4.1 (VIN), U4.4 (!SHDN!)
VUSB: F1.1, Q3.2 (S)

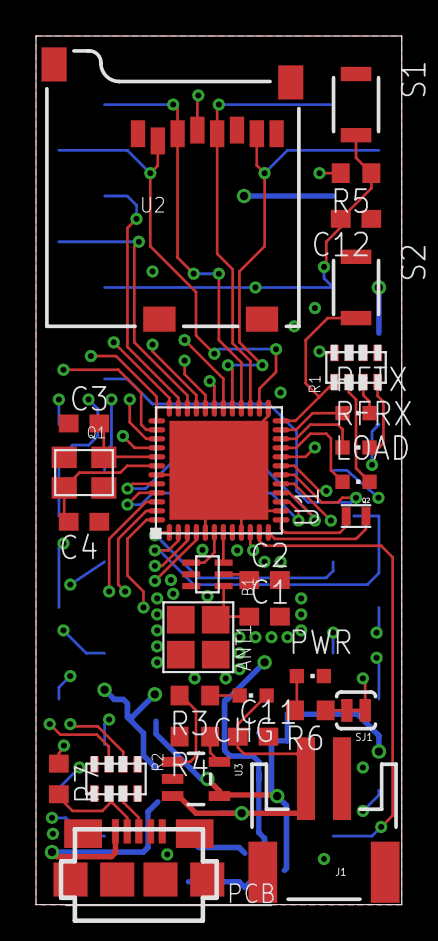
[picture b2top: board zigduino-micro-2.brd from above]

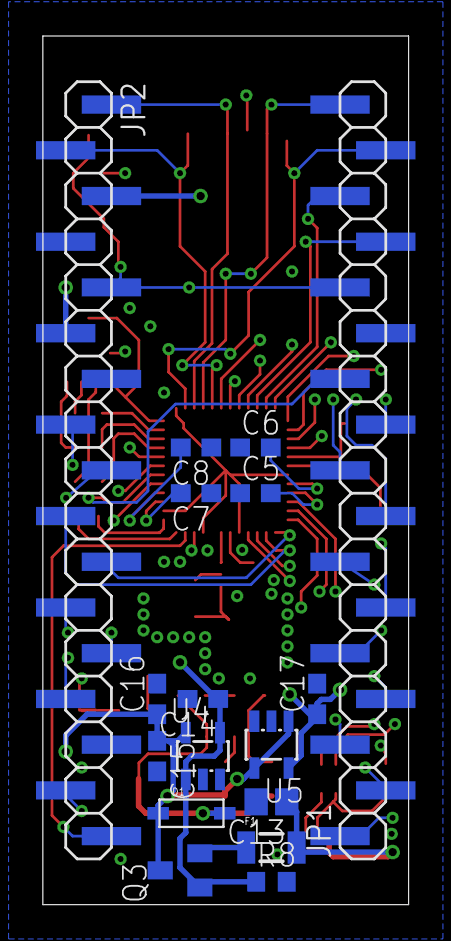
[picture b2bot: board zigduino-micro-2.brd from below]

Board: 4 copper layers, 20.3 x 48.3 mm, 47 parts (17 on the bottom side), 59 nets.

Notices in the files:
Main/zigduino-r3a.brd:
(c) 2012 CC-BY-SA-3.0
parts and their libraries:
SparkFun: Licensing: CC v3.0 Share-Alike You are welcome to use this library for commercial purposes.
dicons: Copyright (C) 2004, Bob Starr (rtzaudio@mindspring.com)
